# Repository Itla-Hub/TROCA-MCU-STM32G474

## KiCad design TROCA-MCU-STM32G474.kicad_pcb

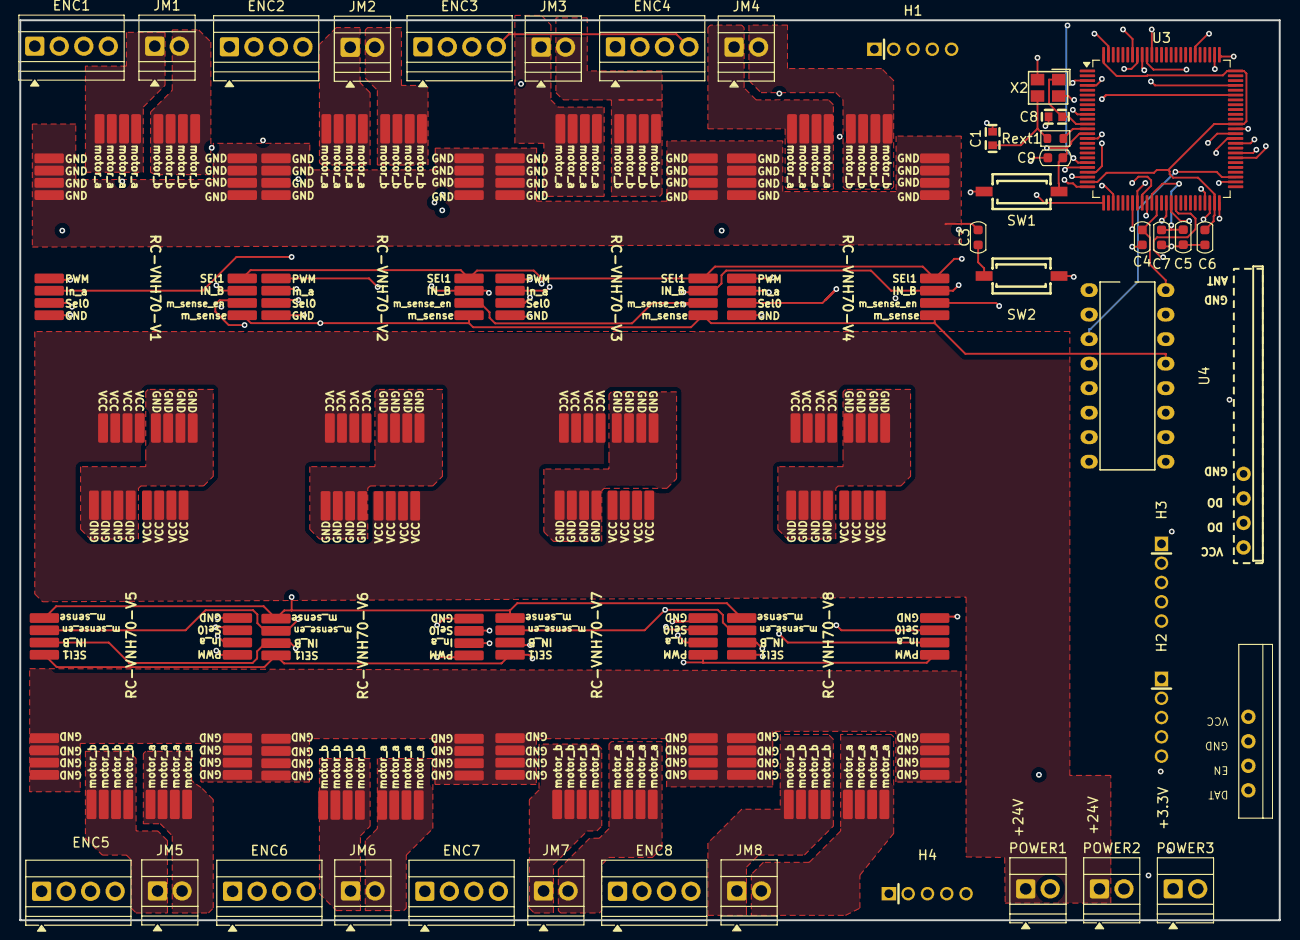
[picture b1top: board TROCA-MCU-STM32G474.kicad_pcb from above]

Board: 4 copper layers, 130.5 x 93.2 mm, 47 parts (0 on the bottom side), 68 nets.

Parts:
C1, C8: 12pF; C0603
C3, C9: 0.1uF; C_0603_1608Metric
C4: 10nF; C_0603_1608Metric
C5: 100nF; C_0603_1608Metric
C6: C_0603; C_0603_1608Metric
C7: 1uF; C_0603_1608Metric
ENC1, ENC2, ENC3, ENC4, ENC5, ENC6, ENC7, ENC8: Screw_Terminal_01x04; TerminalBlock_Xinya_XY308-2.54-4P_1x04_P2.54mm_Horizontal
H1: SWD; HDR-TH_5P-P2.00-V-M
H2, H3: SPI; HDR-TH_5P-P2.00-V-M
H4: USART1; HDR-TH_5P-P2.00-V-M
JM1, JM2, JM3, JM4, JM5, JM6, JM7, JM8: Screw_Terminal_01x02; TerminalBlock_Xinya_XY308-2.54-2P_1x02_P2.54mm_Horizontal
POWER1, POWER2, POWER3: Screw_Terminal_01x02; TerminalBlock_Xinya_XY308-2.54-2P_1x02_P2.54mm_Horizontal
RC-VNH70-V1, RC-VNH70-V2, RC-VNH70-V3, RC-VNH70-V4, RC-VNH70-V5, RC-VNH70-V6, RC-VNH70-V7, RC-VNH70-V8: RC-VNH70-V1
Rext1: R_0603; R_0603_1608Metric
SW1, SW2: HX-3X6X2.5-X SMD TACT SWITCH; SW-SMD_HX-3X6X2.5-X
U1: rf_433mhz_receiver
U2: RF_433MHz_transmisor
U3: STM32G474VETx; LQFP-100_14x14mm_P0.5mm
U4: 74HC4051; PDIP-16_L19.3-W6.4-P2.54-LS7.94-BL
X2: X32258MOB4SI; CRYSTAL-SMD_4P-L3.2-W2.5-BL

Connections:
+3.3V: C4.1, ENC1.4, ENC2.4, ENC3.4, ENC4.4, ENC5.4, ENC6.4, ENC7.4, ENC8.4, H1.1, POWER3.1, U1.3 (VDD), U2.4 (VCC), U3.37 (VDDA), U4.16 (VCC)
+24V: POWER1.1, POWER2.1, RC-VNH70-V1.9 (VCC), RC-VNH70-V1.10 (VCC), RC-VNH70-V1.11 (VCC), RC-VNH70-V1.12 (VCC), RC-VNH70-V2.9 (VCC), RC-VNH70-V2.10 (VCC), RC-VNH70-V2.11 (VCC), RC-VNH70-V2.12 (VCC), RC-VNH70-V3.9 (VCC), RC-VNH70-V3.10 (VCC), RC-VNH70-V3.11 (VCC), RC-VNH70-V3.12 (VCC), RC-VNH70-V4.9 (VCC), RC-VNH70-V4.10 (VCC), RC-VNH70-V4.11 (VCC), RC-VNH70-V4.12 (VCC), RC-VNH70-V5.9 (VCC), RC-VNH70-V5.10 (VCC), RC-VNH70-V5.11 (VCC), RC-VNH70-V5.12 (VCC), RC-VNH70-V6.9 (VCC), RC-VNH70-V6.10 (VCC), RC-VNH70-V6.11 (VCC), RC-VNH70-V6.12 (VCC), RC-VNH70-V7.9 (VCC), RC-VNH70-V7.10 (VCC), RC-VNH70-V7.11 (VCC), RC-VNH70-V7.12 (VCC), RC-VNH70-V8.9 (VCC), RC-VNH70-V8.10 (VCC), RC-VNH70-V8.11 (VCC), RC-VNH70-V8.12 (VCC)
/A1: JM1.1, RC-VNH70-V1.29 (motor_a), RC-VNH70-V1.30 (motor_a), RC-VNH70-V1.31 (motor_a), RC-VNH70-V1.32 (motor_a)
/A2: JM2.1, RC-VNH70-V2.29 (motor_a), RC-VNH70-V2.30 (motor_a), RC-VNH70-V2.31 (motor_a), RC-VNH70-V2.32 (motor_a)
/A3: JM3.1, RC-VNH70-V3.29 (motor_a), RC-VNH70-V3.30 (motor_a), RC-VNH70-V3.31 (motor_a), RC-VNH70-V3.32 (motor_a)
/A4: JM4.1, RC-VNH70-V4.29 (motor_a), RC-VNH70-V4.30 (motor_a), RC-VNH70-V4.31 (motor_a), RC-VNH70-V4.32 (motor_a)
/A5: JM5.2, RC-VNH70-V5.29 (motor_a), RC-VNH70-V5.30 (motor_a), RC-VNH70-V5.31 (motor_a), RC-VNH70-V5.32 (motor_a)
/A6: JM6.2, RC-VNH70-V6.29 (motor_a), RC-VNH70-V6.30 (motor_a), RC-VNH70-V6.31 (motor_a), RC-VNH70-V6.32 (motor_a)
/A7: JM7.2, RC-VNH70-V7.29 (motor_a), RC-VNH70-V7.30 (motor_a), RC-VNH70-V7.31 (motor_a), RC-VNH70-V7.32 (motor_a)
/A8: JM8.2, RC-VNH70-V8.29 (motor_a), RC-VNH70-V8.30 (motor_a), RC-VNH70-V8.31 (motor_a), RC-VNH70-V8.32 (motor_a)
/B1: JM1.2, RC-VNH70-V1.25 (motor_b), RC-VNH70-V1.26 (motor_b), RC-VNH70-V1.27 (motor_b), RC-VNH70-V1.28 (motor_b)
/B2: JM2.2, RC-VNH70-V2.25 (motor_b), RC-VNH70-V2.26 (motor_b), RC-VNH70-V2.27 (motor_b), RC-VNH70-V2.28 (motor_b)
/B3: JM3.2, RC-VNH70-V3.25 (motor_b), RC-VNH70-V3.26 (motor_b), RC-VNH70-V3.27 (motor_b), RC-VNH70-V3.28 (motor_b)
/B4: JM4.2, RC-VNH70-V4.25 (motor_b), RC-VNH70-V4.26 (motor_b), RC-VNH70-V4.27 (motor_b), RC-VNH70-V4.28 (motor_b)
/B5: JM5.1, RC-VNH70-V5.25 (motor_b), RC-VNH70-V5.26 (motor_b), RC-VNH70-V5.27 (motor_b), RC-VNH70-V5.28 (motor_b)
/B6: JM6.1, RC-VNH70-V6.25 (motor_b), RC-VNH70-V6.26 (motor_b), RC-VNH70-V6.27 (motor_b), RC-VNH70-V6.28 (motor_b)
/B7: JM7.1, RC-VNH70-V7.25 (motor_b), RC-VNH70-V7.26 (motor_b), RC-VNH70-V7.27 (motor_b), RC-VNH70-V7.28 (motor_b)
/B8: JM8.1, RC-VNH70-V8.25 (motor_b), RC-VNH70-V8.26 (motor_b), RC-VNH70-V8.27 (motor_b), RC-VNH70-V8.28 (motor_b)
/BOOT0: C3.1, SW2.2
/CS/SS_0: H3.5, U3.93 (PB6)
/CS/SS_1: H2.1, U3.94 (PB7)
/G_EN: RC-VNH70-V1.18 (m_sense_en), RC-VNH70-V2.18 (m_sense_en), RC-VNH70-V3.18 (m_sense_en), RC-VNH70-V4.18 (m_sense_en), RC-VNH70-V5.18 (m_sense_en), RC-VNH70-V6.18 (m_sense_en), RC-VNH70-V7.18 (m_sense_en), RC-VNH70-V8.18 (m_sense_en), U3.70 (PA9)
/G_SEL_0: RC-VNH70-V1.7 (SEL_0), RC-VNH70-V2.7 (SEL_0), RC-VNH70-V3.7 (SEL_0), RC-VNH70-V4.7 (SEL_0), RC-VNH70-V5.7 (SEL_0), RC-VNH70-V6.7 (SEL_0), RC-VNH70-V7.7 (SEL_0), RC-VNH70-V8.7 (SEL_0), U3.71 (PA10)
/G_SEL_1: RC-VNH70-V1.20 (SEL_1), RC-VNH70-V2.20 (SEL_1), RC-VNH70-V3.20 (SEL_1), RC-VNH70-V4.20 (SEL_1), RC-VNH70-V5.20 (SEL_1), RC-VNH70-V6.20 (SEL_1), RC-VNH70-V7.20 (SEL_1), RC-VNH70-V8.20 (SEL_1), U3.72 (PA11)
/MOTOR1_ENCA: ENC1.1, U3.20 (PA0)
/MOTOR1_ENCB: ENC1.2, U3.21 (PA1)
/MOTOR1_INA: RC-VNH70-V1.6 (In_A), RC-VNH70-V2.6 (In_A), RC-VNH70-V3.6 (In_A), RC-VNH70-V4.6 (In_A), RC-VNH70-V5.6 (In_A), RC-VNH70-V6.6 (In_A), RC-VNH70-V7.6 (In_A), RC-VNH70-V8.6 (In_A), U3.40 (PE9)
/MOTOR1_INB: RC-VNH70-V1.19 (in_B), RC-VNH70-V2.19 (in_B), RC-VNH70-V3.19 (in_B), RC-VNH70-V4.19 (in_B), RC-VNH70-V5.19 (in_B), RC-VNH70-V6.19 (in_B), RC-VNH70-V7.19 (in_B), RC-VNH70-V8.19 (in_B), U3.41 (PE10)
/MOTOR2_ENCA: ENC2.1, U3.22 (PA2)
/MOTOR2_ENCB: ENC2.2, U3.25 (PA3)
/MOTOR3_ENCA: ENC3.1, U3.28 (PA6)
/MOTOR3_ENCB: ENC3.2, U3.26 (PA4)
/MOTOR4_ENCA: ENC4.1, U3.3 (PE4)
/MOTOR4_ENCB: ENC4.2, U3.4 (PE5)
/MOTOR5_ENCA: ENC5.1, U3.59 (PD12)
/MOTOR5_ENCB: ENC5.2, U3.60 (PD13)
/MOTOR6_ENCA: ENC6.1, U3.61 (PD14)
/MOTOR6_ENCB: ENC6.2, U3.62 (PD15)
/MOTOR7_ENCA: ENC7.1, U3.34 (PB2)
/MOTOR7_ENCB: ENC7.2, U3.81 (PC12)
/MOTOR8_ENCA: ENC8.1, U3.39 (PE8)
/MOTOR8_ENCB: ENC8.2, U3.10 (PF9)
/MUX_S0: U3.78 (PA15), U4.11 (S0)
/MUX_S1: U3.32 (PB0), U4.10 (S1)
/MUX_S2: U3.33 (PB1), U4.9 (S2)
/MultiSense: U3.53 (PB14), U4.3 (A)
/NRST: C9.1, H1.4, SW1.2, U3.14 (PG10)
/OSC_IN: C8.1, U3.12 (PF0), X2.1
/OSC_OUT: Rext1.2, U3.13 (PF1)
/RF_DIN_0: U1.5 (DO), U3.57 (PD10)
/RF_DIN_1: U1.4 (DO), U3.58 (PD11)
/RF_DOUT_0: U2.1 (DAT), U3.30 (PC4)
/RF_EN: U2.2 (EN), U3.31 (PC5)
/SPI1_MISO: H3.4, U3.91 (PB4)
/SPI1_MOSI: H3.3, U3.92 (PB5)
/SPI1_SCK: H3.2, U3.90 (PB3)
/SWCLK-JTCK: H1.3, U3.77 (PA14)
/SWDIO-JTMS: H1.2, U3.76 (PA13)
/SenseM1: RC-VNH70-V1.17 (m_sense), RC-VNH70-V2.17 (m_sense), RC-VNH70-V3.17 (m_sense), RC-VNH70-V4.17 (m_sense), RC-VNH70-V5.17 (m_sense), RC-VNH70-V6.17 (m_sense), RC-VNH70-V7.17 (m_sense), RC-VNH70-V8.17 (m_sense), U4.13 (A0)
/TIM1_CH1: RC-VNH70-V1.5 (PWM), RC-VNH70-V2.5 (PWM), RC-VNH70-V3.5 (PWM), RC-VNH70-V4.5 (PWM), RC-VNH70-V5.5 (PWM), RC-VNH70-V6.5 (PWM), RC-VNH70-V7.5 (PWM), RC-VNH70-V8.5 (PWM), U3.15 (PC0)
/USART3_CK: H4.2, U3.51 (PB12)
/USART3_RX: H4.4, U3.50 (PB11)
/USART3_TX: H4.3, U3.47 (PB10)
/VDD: C6.1, U3.24 (VDD), U3.49 (VDD), U3.64 (VDD), U3.75 (VDD), U3.100 (VDD)
/VREF+: C5.1, C7.1, U3.36 (VREF+)
/~Mux_EN: U3.52 (PB13), U4.6 (~E)
GND: C1.2, C3.2, C4.2, C5.2, C6.2, C7.2, C8.2, C9.2, ENC1.3, ENC2.3, ENC3.3, ENC4.3, ENC5.3, ENC6.3, ENC7.3, ENC8.3, H1.5, H3.1, H4.1, POWER1.2, POWER2.2, POWER3.2, RC-VNH70-V1.1 (GND), RC-VNH70-V1.2 (GND), RC-VNH70-V1.3 (GND), RC-VNH70-V1.4 (GND), RC-VNH70-V1.8 (GND), RC-VNH70-V1.13 (GND), RC-VNH70-V1.14 (GND), RC-VNH70-V1.15 (GND), RC-VNH70-V1.16 (GND), RC-VNH70-V1.21 (GND), RC-VNH70-V1.22 (GND), RC-VNH70-V1.23 (GND), RC-VNH70-V1.24 (GND), RC-VNH70-V2.1 (GND), RC-VNH70-V2.2 (GND), RC-VNH70-V2.3 (GND), RC-VNH70-V2.4 (GND), RC-VNH70-V2.8 (GND), RC-VNH70-V2.13 (GND), RC-VNH70-V2.14 (GND), RC-VNH70-V2.15 (GND), RC-VNH70-V2.16 (GND), RC-VNH70-V2.21 (GND), RC-VNH70-V2.22 (GND), RC-VNH70-V2.23 (GND), RC-VNH70-V2.24 (GND), RC-VNH70-V3.1 (GND), RC-VNH70-V3.2 (GND), RC-VNH70-V3.3 (GND), RC-VNH70-V3.4 (GND), RC-VNH70-V3.8 (GND), RC-VNH70-V3.13 (GND), RC-VNH70-V3.14 (GND), RC-VNH70-V3.15 (GND), RC-VNH70-V3.16 (GND), RC-VNH70-V3.21 (GND), RC-VNH70-V3.22 (GND), RC-VNH70-V3.23 (GND), RC-VNH70-V3.24 (GND), RC-VNH70-V4.1 (GND), RC-VNH70-V4.2 (GND), RC-VNH70-V4.3 (GND), RC-VNH70-V4.4 (GND), RC-VNH70-V4.8 (GND), RC-VNH70-V4.13 (GND), RC-VNH70-V4.14 (GND), RC-VNH70-V4.15 (GND), RC-VNH70-V4.16 (GND), RC-VNH70-V4.21 (GND), RC-VNH70-V4.22 (GND), RC-VNH70-V4.23 (GND), RC-VNH70-V4.24 (GND), RC-VNH70-V5.1 (GND), RC-VNH70-V5.2 (GND), RC-VNH70-V5.3 (GND), RC-VNH70-V5.4 (GND), RC-VNH70-V5.8 (GND), RC-VNH70-V5.13 (GND), RC-VNH70-V5.14 (GND), RC-VNH70-V5.15 (GND), RC-VNH70-V5.16 (GND), RC-VNH70-V5.21 (GND), RC-VNH70-V5.22 (GND), RC-VNH70-V5.23 (GND), RC-VNH70-V5.24 (GND), RC-VNH70-V6.1 (GND), RC-VNH70-V6.2 (GND), RC-VNH70-V6.3 (GND), RC-VNH70-V6.4 (GND), RC-VNH70-V6.8 (GND), RC-VNH70-V6.13 (GND), RC-VNH70-V6.14 (GND), RC-VNH70-V6.15 (GND), RC-VNH70-V6.16 (GND), RC-VNH70-V6.21 (GND), RC-VNH70-V6.22 (GND), RC-VNH70-V6.23 (GND), RC-VNH70-V6.24 (GND), RC-VNH70-V7.1 (GND), RC-VNH70-V7.2 (GND), RC-VNH70-V7.3 (GND), RC-VNH70-V7.4 (GND), RC-VNH70-V7.8 (GND), RC-VNH70-V7.13 (GND), RC-VNH70-V7.14 (GND), RC-VNH70-V7.15 (GND), RC-VNH70-V7.16 (GND), RC-VNH70-V7.21 (GND), RC-VNH70-V7.22 (GND), RC-VNH70-V7.23 (GND), RC-VNH70-V7.24 (GND), RC-VNH70-V8.1 (GND), RC-VNH70-V8.2 (GND), RC-VNH70-V8.3 (GND), RC-VNH70-V8.4 (GND), RC-VNH70-V8.8 (GND), RC-VNH70-V8.13 (GND), RC-VNH70-V8.14 (GND), RC-VNH70-V8.15 (GND), RC-VNH70-V8.16 (GND), RC-VNH70-V8.21 (GND), RC-VNH70-V8.22 (GND), RC-VNH70-V8.23 (GND), RC-VNH70-V8.24 (GND), SW1.1, SW2.1, U1.6 (GND), U2.3 (GND), U3.23 (VSS), U3.35 (VSSA), U3.48 (VSS), U3.63 (VSS), U3.74 (VSS), U3.99 (VSS), U4.7 (VEE), U4.8 (GND), X2.2 (GND), X2.4 (GND)
unnamed: C1.1, Rext1.1, X2.3

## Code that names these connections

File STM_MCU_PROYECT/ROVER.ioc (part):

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Mcu.Name=STM32G474V(B-C-E)Tx
Mcu.Package=LQFP100
Mcu.UserName=STM32G474VETx
PA0.Signal=S_TIM2_CH1
PA1.Signal=S_TIM2_CH2
PA13.Mode=Serial_Wire
PA13.Signal=SYS_JTMS-SWDIO
PA14.Mode=Serial_Wire
PA14.Signal=SYS_JTCK-SWCLK
PA2.Signal=S_TIM2_CH3
PA3.Signal=S_TIM2_CH4
PA4.Signal=S_TIM3_CH2
PA6.Signal=S_TIM3_CH1
PB10.Mode=Synchronous
PB10.Signal=USART3_TX
PB11.Mode=Synchronous
PB11.Signal=USART3_RX
PB12.Mode=Synchronous
PB12.Signal=USART3_CK
PB2.Signal=S_TIM5_CH1
PB3.Mode=Full_Duplex_Master
PB3.Signal=SPI1_SCK
PB4.Mode=Full_Duplex_Master
PB4.Signal=SPI1_MISO
PB5.Mode=Full_Duplex_Master
PB5.Signal=SPI1_MOSI
PB6.GPIOParameters=GPIO_Label
PB6.GPIO_Label=CS/SS_0
PB6.Signal=GPIO_Output
PB7.GPIOParameters=GPIO_Label
PB7.GPIO_Label=CS/SS_1
PB7.Signal=GPIO_Output
PC0.Signal=S_TIM1_CH1
PC1.Signal=S_TIM1_CH2
PC12.Signal=S_TIM5_CH2
PC2.Signal=S_TIM1_CH3
PC3.Signal=S_TIM1_CH4
PC4.GPIOParameters=GPIO_Label
PC4.GPIO_Label=RF_DOUT_0
PC4.Signal=GPIO_Output
PC5.GPIOParameters=GPIO_Label
PC5.GPIO_Label=RF_EN
PC5.Signal=GPIO_Output
PC6.Signal=S_TIM8_CH1
PC7.Signal=S_TIM8_CH2
PC8.Signal=S_TIM8_CH3
PC9.Signal=S_TIM8_CH4
PD10.GPIOParameters=GPIO_Label
PD10.GPIO_Label=RF_DIN_1
PD10.Signal=GPIO_Input
PD11.GPIOParameters=GPIO_Label
PD11.GPIO_Label=RF_DIN_0
PD11.Signal=GPIO_Input
PD12.Signal=S_TIM4_CH1
PD13.Signal=S_TIM4_CH2
PD14.Signal=S_TIM4_CH3
PD15.Signal=S_TIM4_CH4
PE1.Signal=S_TIM20_CH4
PE2.Signal=S_TIM20_CH1
PE3.Signal=S_TIM20_CH2
PE4.Signal=S_TIM3_CH3
PE5.Signal=S_TIM3_CH4
PE8.Signal=S_TIM5_CH3
PF0-OSC_IN.Mode=HSE-External-Oscillator
PF0-OSC_IN.Signal=RCC_OSC_IN
PF1-OSC_OUT.Mode=HSE-External-Oscillator
PF1-OSC_OUT.Signal=RCC_OSC_OUT
PF2.Signal=S_TIM20_CH3
PF9.Signal=S_TIM5_CH4
RCC.HSE_VALUE=8000000
RCC.SYSCLKFreq_VALUE=16000000
board=custom

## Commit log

2025-11-22 Ajuste de rama
2025-11-22 Datasheet stm32G474 añadido & declaracion de pines
2025-11-22 Delcaracion de INA & INB drivers de motores
2025-11-23 datasheet correcto añadido
2025-11-23 Ajustes de asignacion de pines
2025-11-23 STM_Project_stm32G474VETx
2025-11-23 Integracion de modulos RF
2025-11-23 asignacion de pines terminado
2025-11-23 ajustes 0.1
